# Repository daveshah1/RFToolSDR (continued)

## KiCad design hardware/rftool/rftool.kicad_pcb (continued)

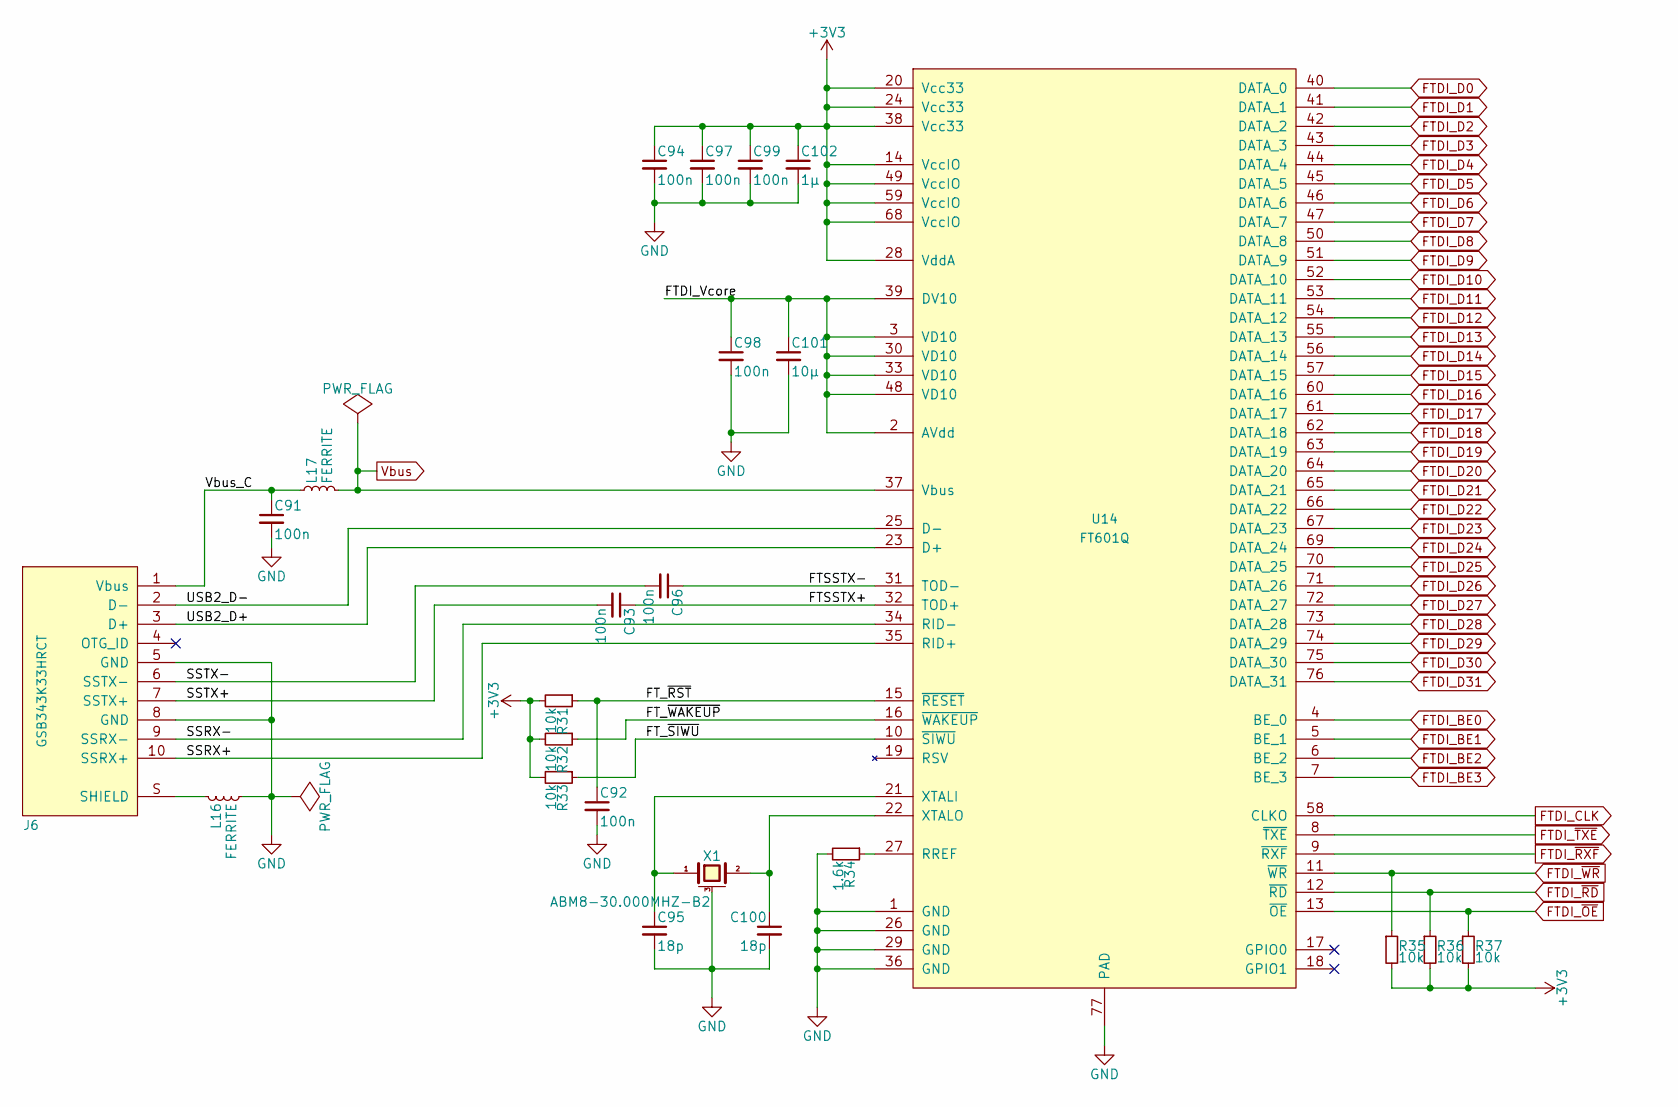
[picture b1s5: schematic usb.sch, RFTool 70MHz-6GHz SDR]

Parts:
C91, C92, C93, C94, C96, C97, C98, C99: 100n; C_0402
C95, C100: 18p; C_0402
C101: 10µ; C_0805
C102: 1µ; C_0603
J6: GSB343K33HRCT; MICROUSB-GSB343K33HRCTV
L16, L17: FERRITE; C_0805
R31, R32, R33, R35, R36, R37: 10k; R_0402
R34: 1.6k; R_0402
U14: FT601Q; QFN_76_pitch0.4mm
X1: ABM8-30.000MHZ-B2; XTAL_ABM8_3.2x2.5mm

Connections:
+3V3: C94.1, C97.1, C99.1, C102.1, R31.2, R32.2, R33.2, R35.2, R36.2, R37.2, U14.14 (VccIO), U14.20 (Vcc33), U14.24 (Vcc33), U14.28 (VddA), U14.38 (Vcc33), U14.49 (VccIO), U14.59 (VccIO), U14.68 (VccIO); also elsewhere on the board
/USB 3.0 I/F/FTDI_Vcore: C98.1, C101.1, U14.2 (AVdd), U14.3 (VD10), U14.30 (VD10), U14.33 (VD10), U14.39 (DV10), U14.48 (VD10)
/USB 3.0 I/F/FTSSTX+: C93.1, U14.32 (TOD+)
/USB 3.0 I/F/FTSSTX-: C96.1, U14.31 (TOD-)
/USB 3.0 I/F/FT_~RST: C92.1, R31.1, U14.15 (~RESET)
/USB 3.0 I/F/FT_~SIWU: R33.1, U14.10 (~SIWU)
/USB 3.0 I/F/FT_~WAKEUP: R32.1, U14.16 (~WAKEUP)
/USB 3.0 I/F/SSRX+: J6.10 (SSRX+), U14.35 (RID+)
/USB 3.0 I/F/SSRX-: J6.9 (SSRX-), U14.34 (RID-)
/USB 3.0 I/F/SSTX+: C93.2, J6.7 (SSTX+)
/USB 3.0 I/F/SSTX-: C96.2, J6.6 (SSTX-)
/USB 3.0 I/F/USB2_D+: J6.3 (D+), U14.23 (D+)
/USB 3.0 I/F/USB2_D-: J6.2 (D-), U14.25 (D-)
/USB 3.0 I/F/Vbus_C: C91.1, J6.1 (Vbus), L17.1
FTDI_BE0: U14.4 (BE_0); also elsewhere on the board
FTDI_BE1: U14.5 (BE_1); also elsewhere on the board
FTDI_BE2: U14.6 (BE_2); also elsewhere on the board
FTDI_BE3: U14.7 (BE_3); also elsewhere on the board
FTDI_CLK: U14.58 (CLKO); also elsewhere on the board
FTDI_D0: U14.40 (DATA_0); also elsewhere on the board
FTDI_D1: U14.41 (DATA_1); also elsewhere on the board
FTDI_D2: U14.42 (DATA_2); also elsewhere on the board
FTDI_D3: U14.43 (DATA_3); also elsewhere on the board
FTDI_D4: U14.44 (DATA_4); also elsewhere on the board
FTDI_D5: U14.45 (DATA_5); also elsewhere on the board
FTDI_D6: U14.46 (DATA_6); also elsewhere on the board
FTDI_D7: U14.47 (DATA_7); also elsewhere on the board
FTDI_D8: U14.50 (DATA_8); also elsewhere on the board
FTDI_D9: U14.51 (DATA_9); also elsewhere on the board
FTDI_D10: U14.52 (DATA_10); also elsewhere on the board
FTDI_D11: U14.53 (DATA_11); also elsewhere on the board
FTDI_D12: U14.54 (DATA_12); also elsewhere on the board
FTDI_D13: U14.55 (DATA_13); also elsewhere on the board
FTDI_D14: U14.56 (DATA_14); also elsewhere on the board
FTDI_D15: U14.57 (DATA_15); also elsewhere on the board
FTDI_D16: U14.60 (DATA_16); also elsewhere on the board
FTDI_D17: U14.61 (DATA_17); also elsewhere on the board
FTDI_D18: U14.62 (DATA_18); also elsewhere on the board
FTDI_D19: U14.63 (DATA_19); also elsewhere on the board
FTDI_D20: U14.64 (DATA_20); also elsewhere on the board
FTDI_D21: U14.65 (DATA_21); also elsewhere on the board
FTDI_D22: U14.66 (DATA_22); also elsewhere on the board
FTDI_D23: U14.67 (DATA_23); also elsewhere on the board
FTDI_D24: U14.69 (DATA_24); also elsewhere on the board
FTDI_D25: U14.70 (DATA_25); also elsewhere on the board
FTDI_D26: U14.71 (DATA_26); also elsewhere on the board
FTDI_D27: U14.72 (DATA_27); also elsewhere on the board
FTDI_D28: U14.73 (DATA_28); also elsewhere on the board
FTDI_D29: U14.74 (DATA_29); also elsewhere on the board
FTDI_D30: U14.75 (DATA_30); also elsewhere on the board
FTDI_D31: U14.76 (DATA_31); also elsewhere on the board
FTDI_~OE: R37.1, U14.13 (~OE); also elsewhere on the board
FTDI_~RD: R36.1, U14.12 (~RD); also elsewhere on the board
FTDI_~RXF: U14.9 (~RXF); also elsewhere on the board
FTDI_~TXE: U14.8 (~TXE); also elsewhere on the board
FTDI_~WR: R35.1, U14.11 (~WR); also elsewhere on the board
GND: C91.2, C92.2, C94.2, C95.2, C97.2, C98.2, C99.2, C100.2, C101.2, C102.2, J6.5 (GND), J6.8 (GND), L16.2, R34.2, U14.1 (GND), U14.26 (GND), U14.29 (GND), U14.36 (GND), U14.77 (PAD), X1.3 (case); also elsewhere on the board
unnamed: C95.1, U14.21 (XTALI), X1.1
unnamed: C100.1, U14.22 (XTALO), X1.2
unnamed: J6.S (SHIELD), L16.1
unnamed: R34.1, U14.27 (RREF)
Vbus: L17.2, U14.37 (Vbus); also elsewhere on the board

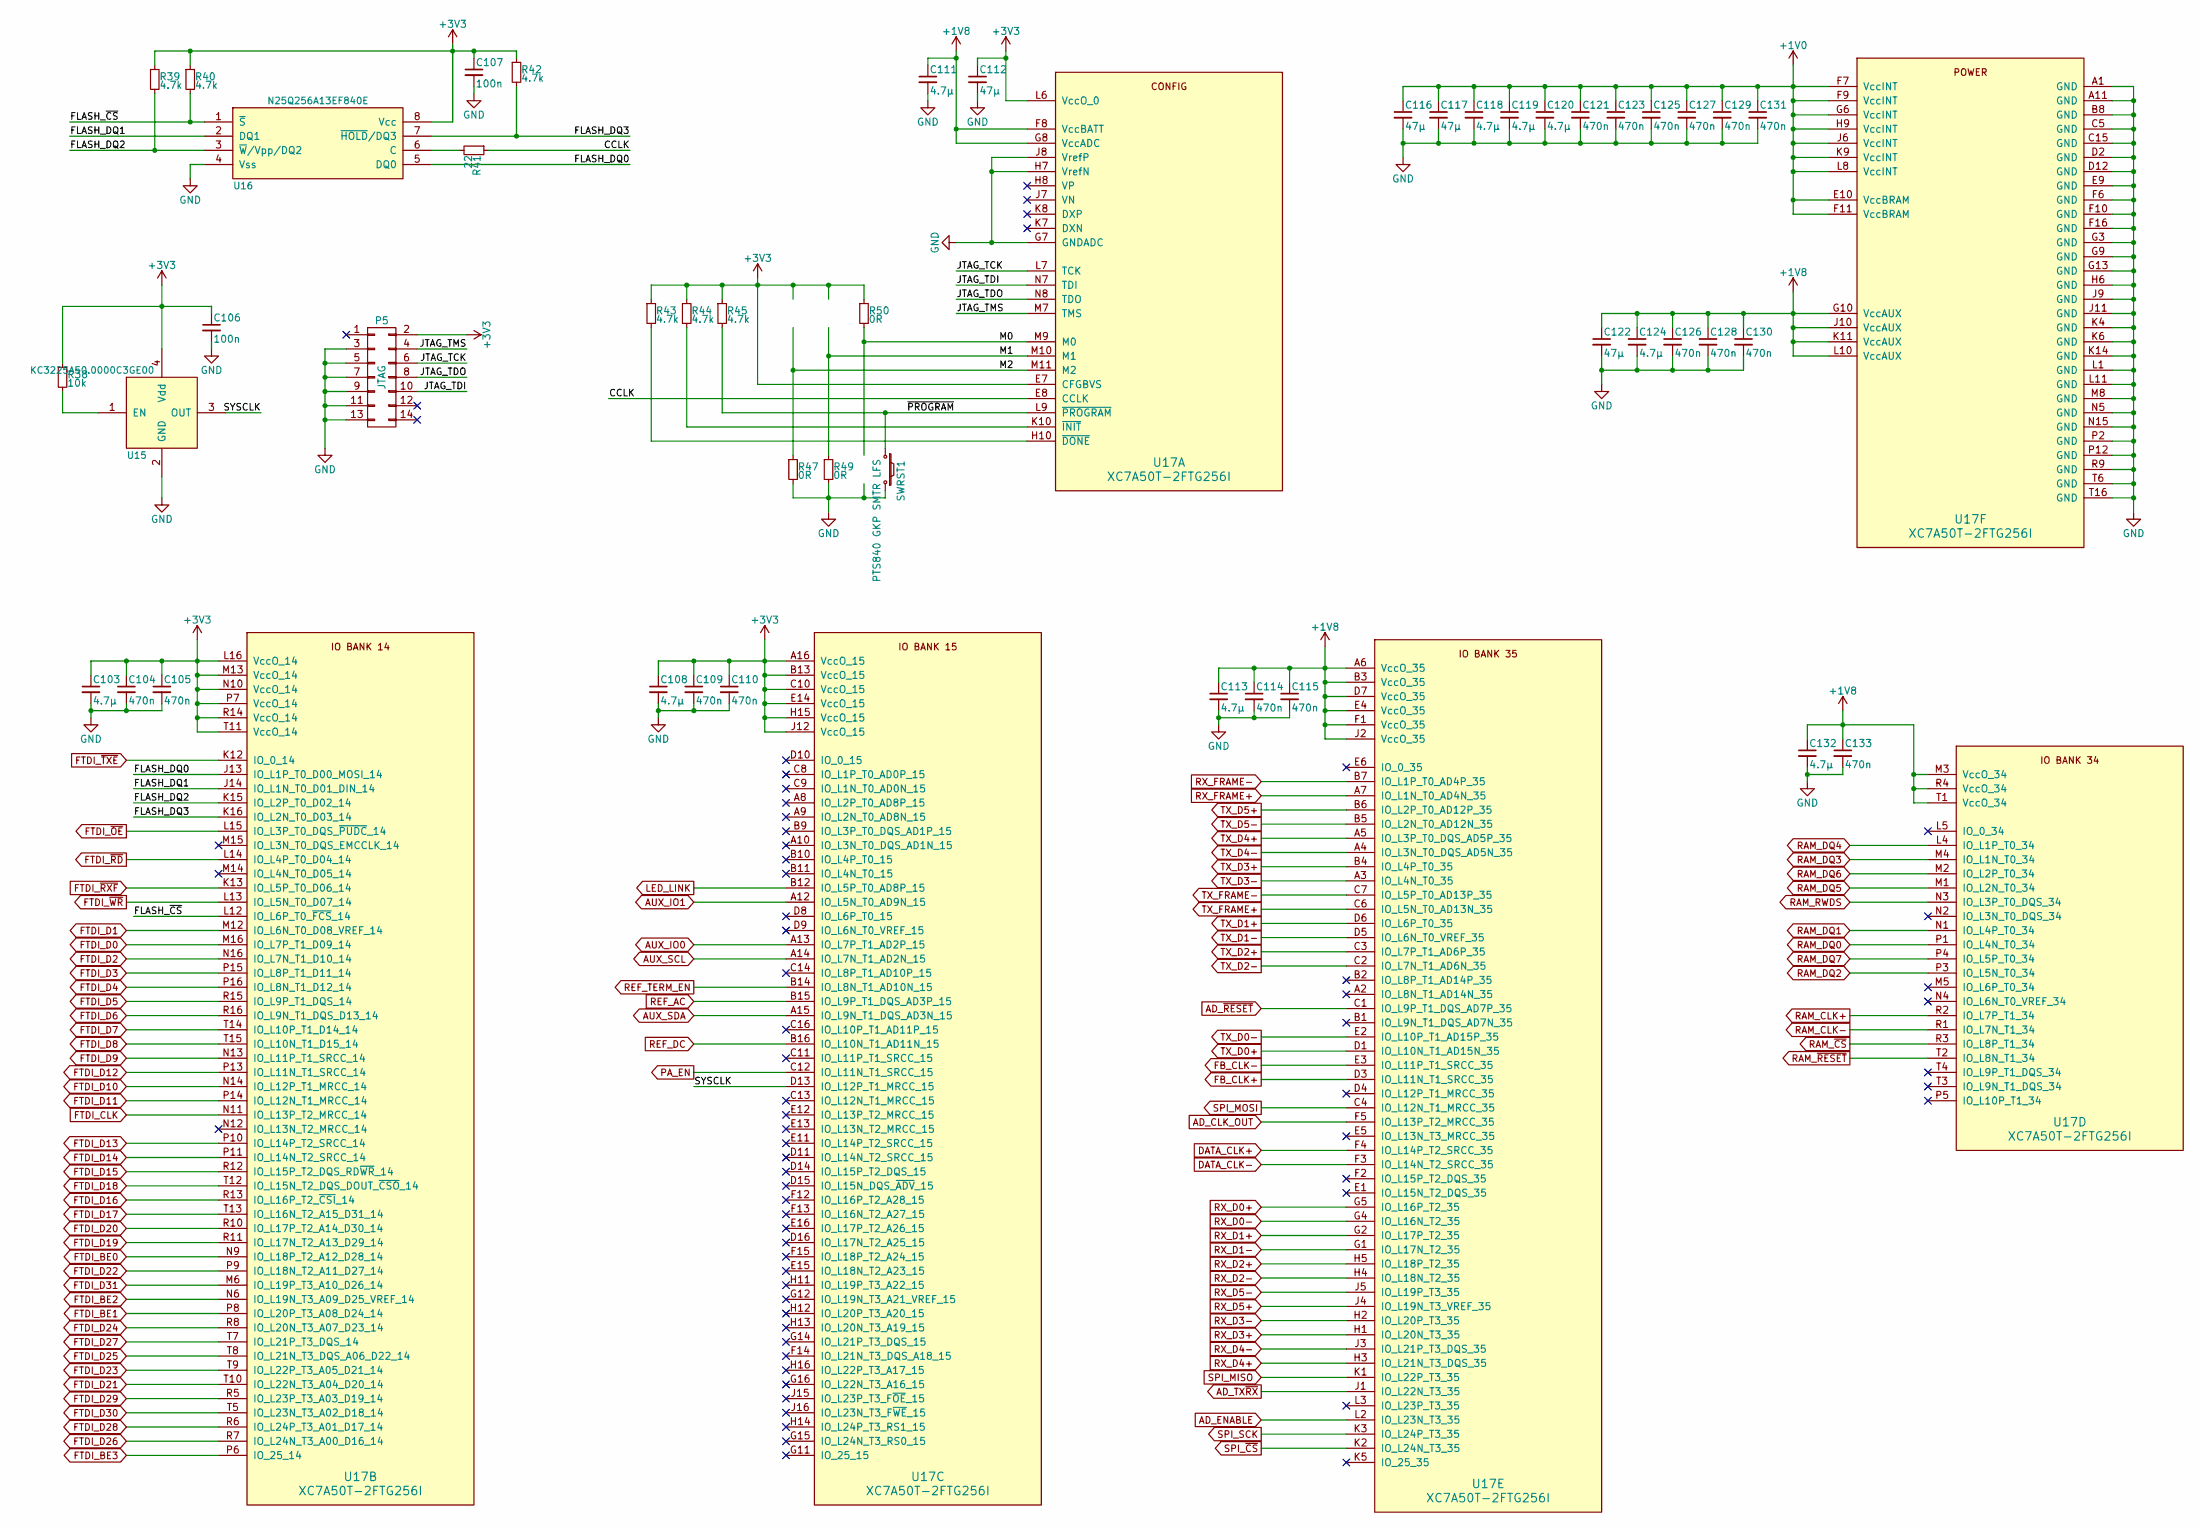
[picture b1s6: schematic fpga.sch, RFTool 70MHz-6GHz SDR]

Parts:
C103, C108, C111, C113, C118, C119, C120, C124, C132: 4.7µ; C_0805
C104, C105, C109, C110, C114, C115, C121, C123, C125, C126, C127, C128, C129, C130, C131, C133: 470n; C_0402
C106, C107: 100n; C_0402
C112, C116, C117, C122: 47µ; C_1206
P5: JTAG; Pin_Header_Straight_2x07_Pitch2.00mm
R38: 10k; R_0402
R39, R40, R42, R43, R44, R45: 4.7k; R_0402
R41: 22; R_0402
R47, R49, R50: 0R; R_0402
SWRST1: PTS840 GKP SMTR LFS; PTS840G
U15: KC3225A50.0000C3GE00; VCTCXO_TX_3.2x2.5mm
U16: N25Q256A13EF840E; VDFPN8
U17: XC7A50T-2FTG256I; BGA-256

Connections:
+1V0: C116.1, C117.1, C118.1, C119.1, C120.1, C121.1, C123.1, C125.1, C127.1, C129.1, C131.1, U17.E10 (VccBRAM), U17.F7 (VccINT), U17.F9 (VccINT), U17.F11 (VccBRAM), U17.G6 (VccINT), U17.H9 (VccINT), U17.J6 (VccINT), U17.K9 (VccINT), U17.L8 (VccINT); also elsewhere on the board
+1V8: C111.1, C113.1, C114.1, C115.1, C122.1, C124.1, C126.1, C128.1, C130.1, C132.1, C133.1, U17.A6 (VccO_35), U17.B3 (VccO_35), U17.D7 (VccO_35), U17.E4 (VccO_35), U17.F1 (VccO_35), U17.F8 (VccBATT), U17.G8 (VccADC), U17.G10 (VccAUX), U17.J2 (VccO_35), U17.J10 (VccAUX), U17.K11 (VccAUX), U17.L10 (VccAUX), U17.M3 (VccO_34), U17.R4 (VccO_34), U17.T1 (VccO_34); also elsewhere on the board
+3V3: C103.1, C104.1, C105.1, C106.1, C107.1, C108.1, C109.1, C110.1, C112.1, P5.2, R38.1, R39.1, R40.1, R42.1, R43.1, R44.1, R45.1, R50.1, U15.4 (Vdd), U16.8 (Vcc), U17.A16 (VccO_15), U17.B13 (VccO_15), U17.C10 (VccO_15), U17.E7 (CFGBVS), U17.E14 (VccO_15), U17.H15 (VccO_15), U17.J12 (VccO_15), U17.L6 (VccO_0), U17.L16 (VccO_14), U17.M13 (VccO_14), U17.N10 (VccO_14), U17.P7 (VccO_14), U17.R14 (VccO_14), U17.T11 (VccO_14); also elsewhere on the board
/Artix 7 FPGA/CCLK: R41.1, U17.E8 (CCLK)
/Artix 7 FPGA/FLASH_DQ0: U16.5 (DQ0), U17.J13 (IO_L1P_T0_D00_MOSI_14)
/Artix 7 FPGA/FLASH_DQ1: U16.2 (DQ1), U17.J14 (IO_L1N_T0_D01_DIN_14)
/Artix 7 FPGA/FLASH_DQ2: R39.2, U16.3 (~W~/Vpp/DQ2), U17.K15 (IO_L2P_T0_D02_14)
/Artix 7 FPGA/FLASH_DQ3: R42.2, U16.7 (~HOLD~/DQ3), U17.K16 (IO_L2N_T0_D03_14)
/Artix 7 FPGA/FLASH_~CS: R40.2, U16.1 (~S), U17.L12 (IO_L6P_T0_~FCS~_14)
/Artix 7 FPGA/JTAG_TCK: P5.6, U17.L7 (TCK)
/Artix 7 FPGA/JTAG_TDI: P5.10, U17.N7 (TDI)
/Artix 7 FPGA/JTAG_TDO: P5.8, U17.N8 (TDO)
/Artix 7 FPGA/JTAG_TMS: P5.4, U17.M7 (TMS)
/Artix 7 FPGA/M0: R50.2, U17.M9 (M0)
/Artix 7 FPGA/M1: R49.1, U17.M10 (M1)
/Artix 7 FPGA/M2: R47.1, U17.M11 (M2)
/Artix 7 FPGA/SYSCLK: U15.3 (OUT), U17.D13 (IO_L12P_T1_MRCC_15)
/Artix 7 FPGA/~PROGRAM: R45.2, SWRST1.1, U17.L9 (~PROGRAM)
AD_CLK_OUT: U17.F5 (IO_L13P_T2_MRCC_35); also elsewhere on the board
AD_ENABLE: U17.L2 (IO_L23N_T3_35); also elsewhere on the board
AD_TX~RX: U17.J1 (IO_L22N_T3_35); also elsewhere on the board
AD_~RESET: U17.C1 (IO_L9P_T1_DQS_AD7P_35); also elsewhere on the board
AUX_IO0: U17.A13 (IO_L7P_T1_AD2P_15); also elsewhere on the board
AUX_IO1: U17.A12 (IO_L5N_T0_AD9N_15); also elsewhere on the board
AUX_SCL: U17.A14 (IO_L7N_T1_AD2N_15); also elsewhere on the board
AUX_SDA: U17.A15 (IO_L9N_T1_DQS_AD3N_15); also elsewhere on the board
DATA_CLK+: U17.F4 (IO_L14P_T2_SRCC_35); also elsewhere on the board
DATA_CLK-: U17.F3 (IO_L14N_T2_SRCC_35); also elsewhere on the board
FB_CLK+: U17.D3 (IO_L11N_T1_SRCC_35); also elsewhere on the board
FB_CLK-: U17.E3 (IO_L11P_T1_SRCC_35); also elsewhere on the board
FTDI_BE0: U17.N9 (IO_L18P_T2_A12_D28_14); also elsewhere on the board
FTDI_BE1: U17.P8 (IO_L20P_T3_A08_D24_14); also elsewhere on the board
FTDI_BE2: U17.N6 (IO_L19N_T3_A09_D25_VREF_14); also elsewhere on the board
FTDI_BE3: U17.P6 (IO_25_14); also elsewhere on the board
FTDI_CLK: U17.N11 (IO_L13P_T2_MRCC_14); also elsewhere on the board
FTDI_D0: U17.M16 (IO_L7P_T1_D09_14); also elsewhere on the board
FTDI_D1: U17.M12 (IO_L6N_T0_D08_VREF_14); also elsewhere on the board
FTDI_D2: U17.N16 (IO_L7N_T1_D10_14); also elsewhere on the board
FTDI_D3: U17.P15 (IO_L8P_T1_D11_14); also elsewhere on the board
FTDI_D4: U17.P16 (IO_L8N_T1_D12_14); also elsewhere on the board
FTDI_D5: U17.R15 (IO_L9P_T1_DQS_14); also elsewhere on the board
FTDI_D6: U17.R16 (IO_L9N_T1_DQS_D13_14); also elsewhere on the board
FTDI_D7: U17.T14 (IO_L10P_T1_D14_14); also elsewhere on the board
FTDI_D8: U17.T15 (IO_L10N_T1_D15_14); also elsewhere on the board
FTDI_D9: U17.N13 (IO_L11P_T1_SRCC_14); also elsewhere on the board
FTDI_D10: U17.N14 (IO_L12P_T1_MRCC_14); also elsewhere on the board
FTDI_D11: U17.P14 (IO_L12N_T1_MRCC_14); also elsewhere on the board
FTDI_D12: U17.P13 (IO_L11N_T1_SRCC_14); also elsewhere on the board
FTDI_D13: U17.P10 (IO_L14P_T2_SRCC_14); also elsewhere on the board
FTDI_D14: U17.P11 (IO_L14N_T2_SRCC_14); also elsewhere on the board
FTDI_D15: U17.R12 (IO_L15P_T2_DQS_RD~WR~_14); also elsewhere on the board
FTDI_D16: U17.R13 (IO_L16P_T2_~CSI~_14); also elsewhere on the board
FTDI_D17: U17.T13 (IO_L16N_T2_A15_D31_14); also elsewhere on the board
FTDI_D18: U17.T12 (IO_L15N_T2_DQS_DOUT_~CSO~_14); also elsewhere on the board
FTDI_D19: U17.R11 (IO_L17N_T2_A13_D29_14); also elsewhere on the board
FTDI_D20: U17.R10 (IO_L17P_T2_A14_D30_14); also elsewhere on the board
FTDI_D21: U17.T10 (IO_L22N_T3_A04_D20_14); also elsewhere on the board
FTDI_D22: U17.P9 (IO_L18N_T2_A11_D27_14); also elsewhere on the board
FTDI_D23: U17.T9 (IO_L22P_T3_A05_D21_14); also elsewhere on the board
FTDI_D24: U17.R8 (IO_L20N_T3_A07_D23_14); also elsewhere on the board
FTDI_D25: U17.T8 (IO_L21N_T3_DQS_A06_D22_14); also elsewhere on the board
FTDI_D26: U17.R7 (IO_L24N_T3_A00_D16_14); also elsewhere on the board
FTDI_D27: U17.T7 (IO_L21P_T3_DQS_14); also elsewhere on the board
FTDI_D28: U17.R6 (IO_L24P_T3_A01_D17_14); also elsewhere on the board
FTDI_D29: U17.R5 (IO_L23P_T3_A03_D19_14); also elsewhere on the board
FTDI_D30: U17.T5 (IO_L23N_T3_A02_D18_14); also elsewhere on the board
FTDI_D31: U17.M6 (IO_L19P_T3_A10_D26_14); also elsewhere on the board
FTDI_~OE: U17.L15 (IO_L3P_T0_DQS_~PUDC~_14); also elsewhere on the board
FTDI_~RD: U17.L14 (IO_L4P_T0_D04_14); also elsewhere on the board
FTDI_~RXF: U17.K13 (IO_L5P_T0_D06_14); also elsewhere on the board
FTDI_~TXE: U17.K12 (IO_0_14); also elsewhere on the board
FTDI_~WR: U17.L13 (IO_L5N_T0_D07_14); also elsewhere on the board
GND: C103.2, C104.2, C105.2, C106.2, C107.2, C108.2, C109.2, C110.2, C111.2, C112.2, C113.2, C114.2, C115.2, C116.2, C117.2, C118.2, C119.2, C120.2, C121.2, C122.2, C123.2, C124.2, C125.2, C126.2, C127.2, C128.2, C129.2, C130.2, C131.2, C132.2, C133.2, P5.3, P5.5, P5.7, P5.9, P5.11, P5.13, R47.2, R49.2, SWRST1.2, U15.2 (GND), U16.4 (Vss), U17.A1 (GND), U17.A11 (GND), U17.B8 (GND), U17.C5 (GND), U17.C15 (GND), U17.D2 (GND), U17.D12 (GND), U17.E9 (GND), U17.F6 (GND), U17.F10 (GND), U17.F16 (GND), U17.G3 (GND), U17.G7 (GNDADC), U17.G9 (GND), U17.G13 (GND), U17.H6 (GND), U17.H7 (VrefN), U17.J8 (VrefP), U17.J9 (GND), U17.J11 (GND), U17.K4 (GND), U17.K6 (GND), U17.K14 (GND), U17.L1 (GND), U17.L11 (GND), U17.M8 (GND), U17.N5 (GND), U17.N15 (GND), U17.P2 (GND), U17.P12 (GND), U17.R9 (GND), U17.T6 (GND), U17.T16 (GND); also elsewhere on the board
LED_LINK: U17.B12 (IO_L5P_T0_AD8P_15); also elsewhere on the board
unnamed: R38.2, U15.1 (EN)
unnamed: R41.2, U16.6 (C)
unnamed: R43.2, U17.H10 (~DONE)
unnamed: R44.2, U17.K10 (~INIT)
PA_EN: U17.C12 (IO_L11N_T1_SRCC_15); also elsewhere on the board
RAM_CLK+: U17.R2 (IO_L7P_T1_34); also elsewhere on the board
RAM_CLK-: U17.R1 (IO_L7N_T1_34); also elsewhere on the board
RAM_DQ0: U17.P1 (IO_L4N_T0_34); also elsewhere on the board
RAM_DQ1: U17.N1 (IO_L4P_T0_34); also elsewhere on the board
RAM_DQ2: U17.P3 (IO_L5N_T0_34); also elsewhere on the board
RAM_DQ3: U17.M4 (IO_L1N_T0_34); also elsewhere on the board
RAM_DQ4: U17.L4 (IO_L1P_T0_34); also elsewhere on the board
RAM_DQ5: U17.M1 (IO_L2N_T0_34); also elsewhere on the board
RAM_DQ6: U17.M2 (IO_L2P_T0_34); also elsewhere on the board
RAM_DQ7: U17.P4 (IO_L5P_T0_34); also elsewhere on the board
RAM_RWDS: U17.N3 (IO_L3P_T0_DQS_34); also elsewhere on the board
RAM_~CS: U17.R3 (IO_L8P_T1_34); also elsewhere on the board
RAM_~RESET: U17.T2 (IO_L8N_T1_34); also elsewhere on the board
REF_AC: U17.B15 (IO_L9P_T1_DQS_AD3P_15); also elsewhere on the board
REF_DC: U17.B16 (IO_L10N_T1_AD11N_15); also elsewhere on the board
REF_TERM_EN: U17.B14 (IO_L8N_T1_AD10N_15); also elsewhere on the board
RX_D0+: U17.G5 (IO_L16P_T2_35); also elsewhere on the board
RX_D0-: U17.G4 (IO_L16N_T2_35); also elsewhere on the board
RX_D1+: U17.G2 (IO_L17P_T2_35); also elsewhere on the board
RX_D1-: U17.G1 (IO_L17N_T2_35); also elsewhere on the board
RX_D2+: U17.H5 (IO_L18P_T2_35); also elsewhere on the board
RX_D2-: U17.H4 (IO_L18N_T2_35); also elsewhere on the board
RX_D3+: U17.H1 (IO_L20N_T3_35); also elsewhere on the board
RX_D3-: U17.H2 (IO_L20P_T3_35); also elsewhere on the board
RX_D4+: U17.H3 (IO_L21N_T3_DQS_35); also elsewhere on the board
RX_D4-: U17.J3 (IO_L21P_T3_DQS_35); also elsewhere on the board
RX_D5+: U17.J4 (IO_L19N_T3_VREF_35); also elsewhere on the board
RX_D5-: U17.J5 (IO_L19P_T3_35); also elsewhere on the board
RX_FRAME+: U17.A7 (IO_L1N_T0_AD4N_35); also elsewhere on the board
RX_FRAME-: U17.B7 (IO_L1P_T0_AD4P_35); also elsewhere on the board
SPI_MISO: U17.K1 (IO_L22P_T3_35); also elsewhere on the board
SPI_MOSI: U17.C4 (IO_L12N_T1_MRCC_35); also elsewhere on the board
SPI_SCK: U17.K3 (IO_L24P_T3_35); also elsewhere on the board
SPI_~CS: U17.K2 (IO_L24N_T3_35); also elsewhere on the board
TX_D0+: U17.D1 (IO_L10N_T1_AD15N_35); also elsewhere on the board
TX_D0-: U17.E2 (IO_L10P_T1_AD15P_35); also elsewhere on the board
TX_D1+: U17.D6 (IO_L6P_T0_35); also elsewhere on the board
TX_D1-: U17.D5 (IO_L6N_T0_VREF_35); also elsewhere on the board
TX_D2+: U17.C3 (IO_L7P_T1_AD6P_35); also elsewhere on the board
TX_D2-: U17.C2 (IO_L7N_T1_AD6N_35); also elsewhere on the board
TX_D3+: U17.B4 (IO_L4P_T0_35); also elsewhere on the board
TX_D3-: U17.A3 (IO_L4N_T0_35); also elsewhere on the board
TX_D4+: U17.A5 (IO_L3P_T0_DQS_AD5P_35); also elsewhere on the board
TX_D4-: U17.A4 (IO_L3N_T0_DQS_AD5N_35); also elsewhere on the board
TX_D5+: U17.B6 (IO_L2P_T0_AD12P_35); also elsewhere on the board
TX_D5-: U17.B5 (IO_L2N_T0_AD12N_35); also elsewhere on the board
TX_FRAME+: U17.C6 (IO_L5N_T0_AD13N_35); also elsewhere on the board
TX_FRAME-: U17.C7 (IO_L5P_T0_AD13P_35); also elsewhere on the board

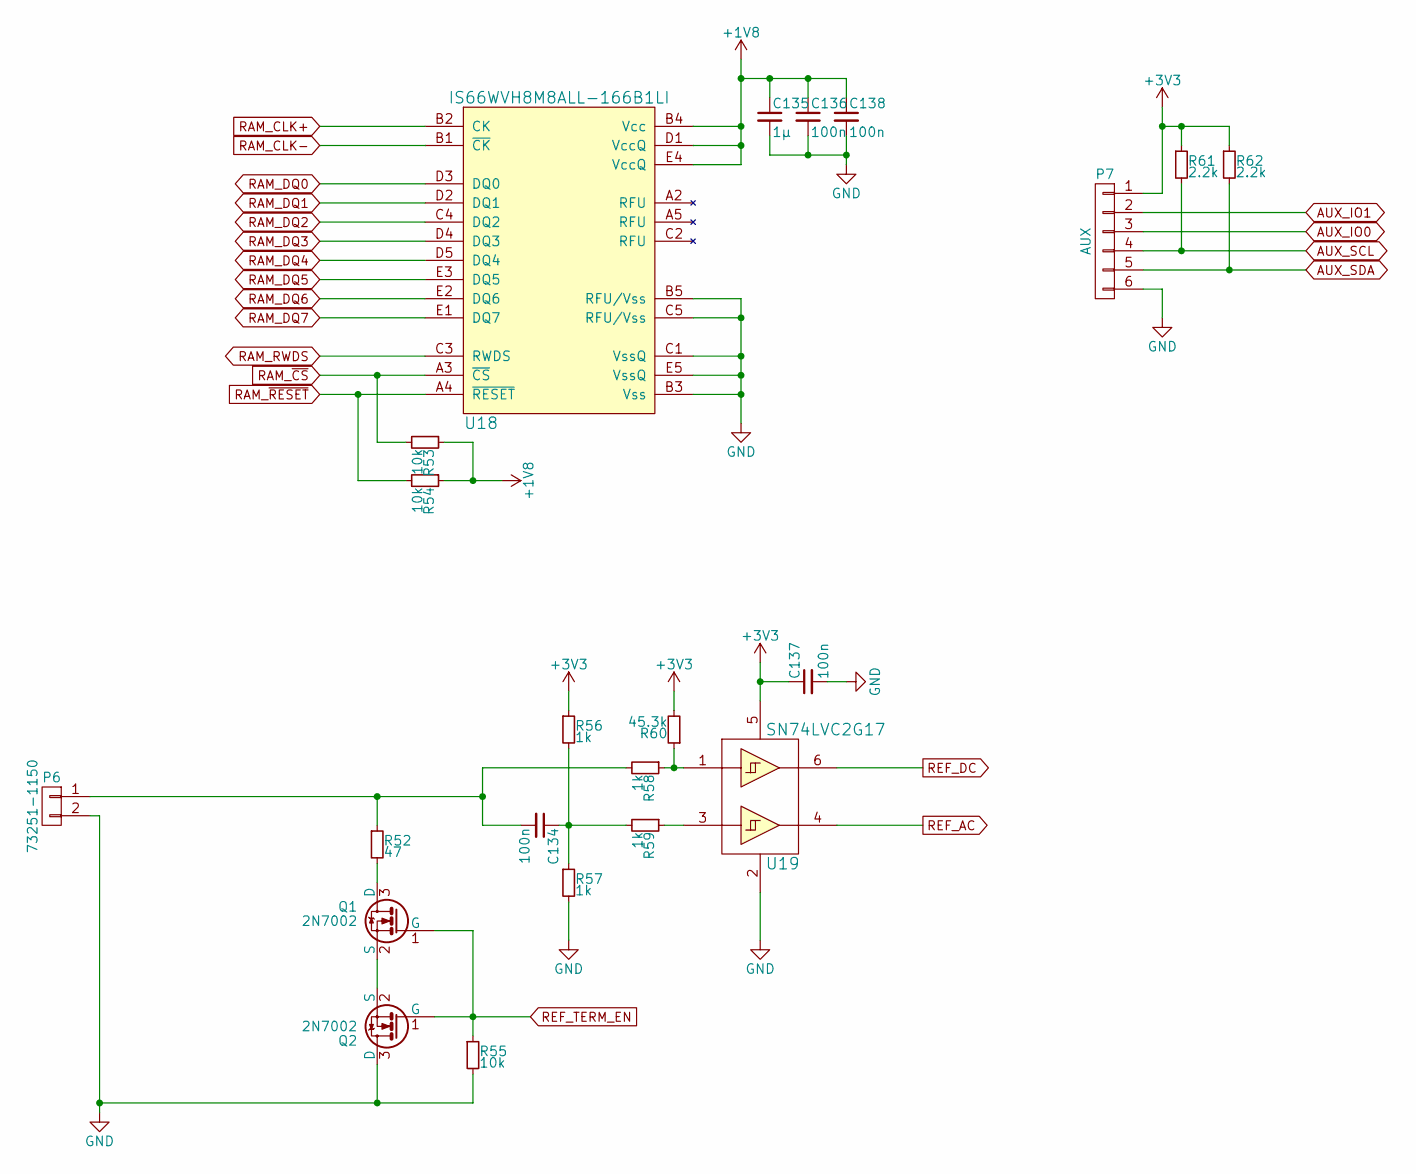
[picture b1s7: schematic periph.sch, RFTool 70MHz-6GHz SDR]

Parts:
C134, C136, C137, C138: 100n; C_0402
C135: 1µ; C_0603
P6: 73251-1150; SMA-EDGE-73251-1150
P7: AUX; Pin_Header_Angled_1x06
Q1, Q2: 2N7002; SOT-23
R52: 47; R_0402
R53, R54, R55: 10k; R_0402
R56, R57, R58, R59: 1k; R_0402
R60: 45.3k; R_0402
R61, R62: 2.2k; R_0402
U18: IS66WVH8M8ALL-166B1LI; FBGA24_pitch1mm
U19: SN74LVC2G17; SOT-23-6

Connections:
+1V8: C135.1, C136.1, C138.1, R53.1, R54.1, U18.B4 (Vcc), U18.D1 (VccQ), U18.E4 (VccQ); also elsewhere on the board
+3V3: C137.1, P7.1, R56.1, R60.2, R61.1, R62.1, U19.5 (Vcc); also elsewhere on the board
AUX_IO0: P7.3; also elsewhere on the board
AUX_IO1: P7.2; also elsewhere on the board
AUX_SCL: P7.4, R61.2; also elsewhere on the board
AUX_SDA: P7.5, R62.2; also elsewhere on the board
GND: C135.2, C136.2, C137.2, C138.2, P6.2, P7.6, Q2.3 (D), R55.2, R57.2, U18.B3 (Vss), U18.B5 (RFU/Vss), U18.C1 (VssQ), U18.C5 (RFU/Vss), U18.E5 (VssQ), U19.2 (GND); also elsewhere on the board
unnamed: C134.1, R56.2, R57.1, R59.2
unnamed: C134.2, P6.1, R52.1, R58.2
unnamed: Q1.2 (S), Q2.2 (S)
unnamed: Q1.3 (D), R52.2
unnamed: R58.1, R60.1, U19.1 (1A)
unnamed: R59.1, U19.3 (2A)
RAM_CLK+: U18.B2 (CK); also elsewhere on the board
RAM_CLK-: U18.B1 (~CK); also elsewhere on the board
RAM_DQ0: U18.D3 (DQ0); also elsewhere on the board
RAM_DQ1: U18.D2 (DQ1); also elsewhere on the board
RAM_DQ2: U18.C4 (DQ2); also elsewhere on the board
RAM_DQ3: U18.D4 (DQ3); also elsewhere on the board
RAM_DQ4: U18.D5 (DQ4); also elsewhere on the board
RAM_DQ5: U18.E3 (DQ5); also elsewhere on the board
RAM_DQ6: U18.E2 (DQ6); also elsewhere on the board
RAM_DQ7: U18.E1 (DQ7); also elsewhere on the board
RAM_RWDS: U18.C3 (RWDS); also elsewhere on the board
RAM_~CS: R53.2, U18.A3 (~CS); also elsewhere on the board
RAM_~RESET: R54.2, U18.A4 (~RESET); also elsewhere on the board
REF_AC: U19.4 (Y); also elsewhere on the board
REF_DC: U19.6 (1Y); also elsewhere on the board
REF_TERM_EN: Q1.1 (G), Q2.1 (G), R55.1; also elsewhere on the board

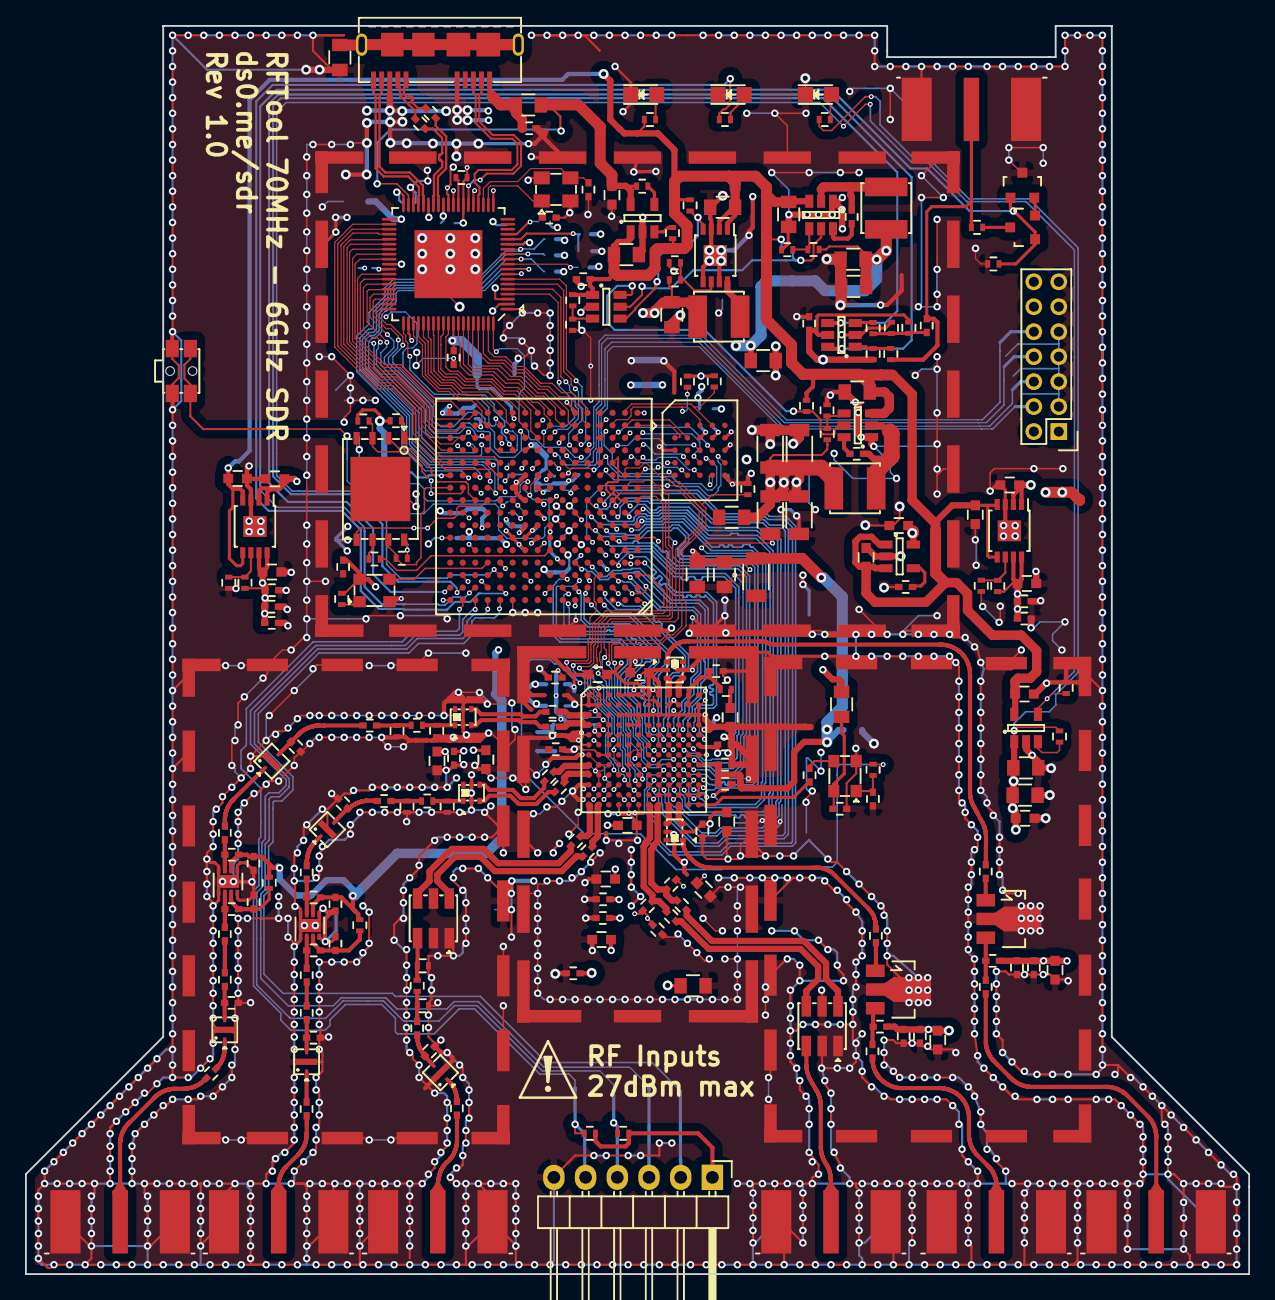
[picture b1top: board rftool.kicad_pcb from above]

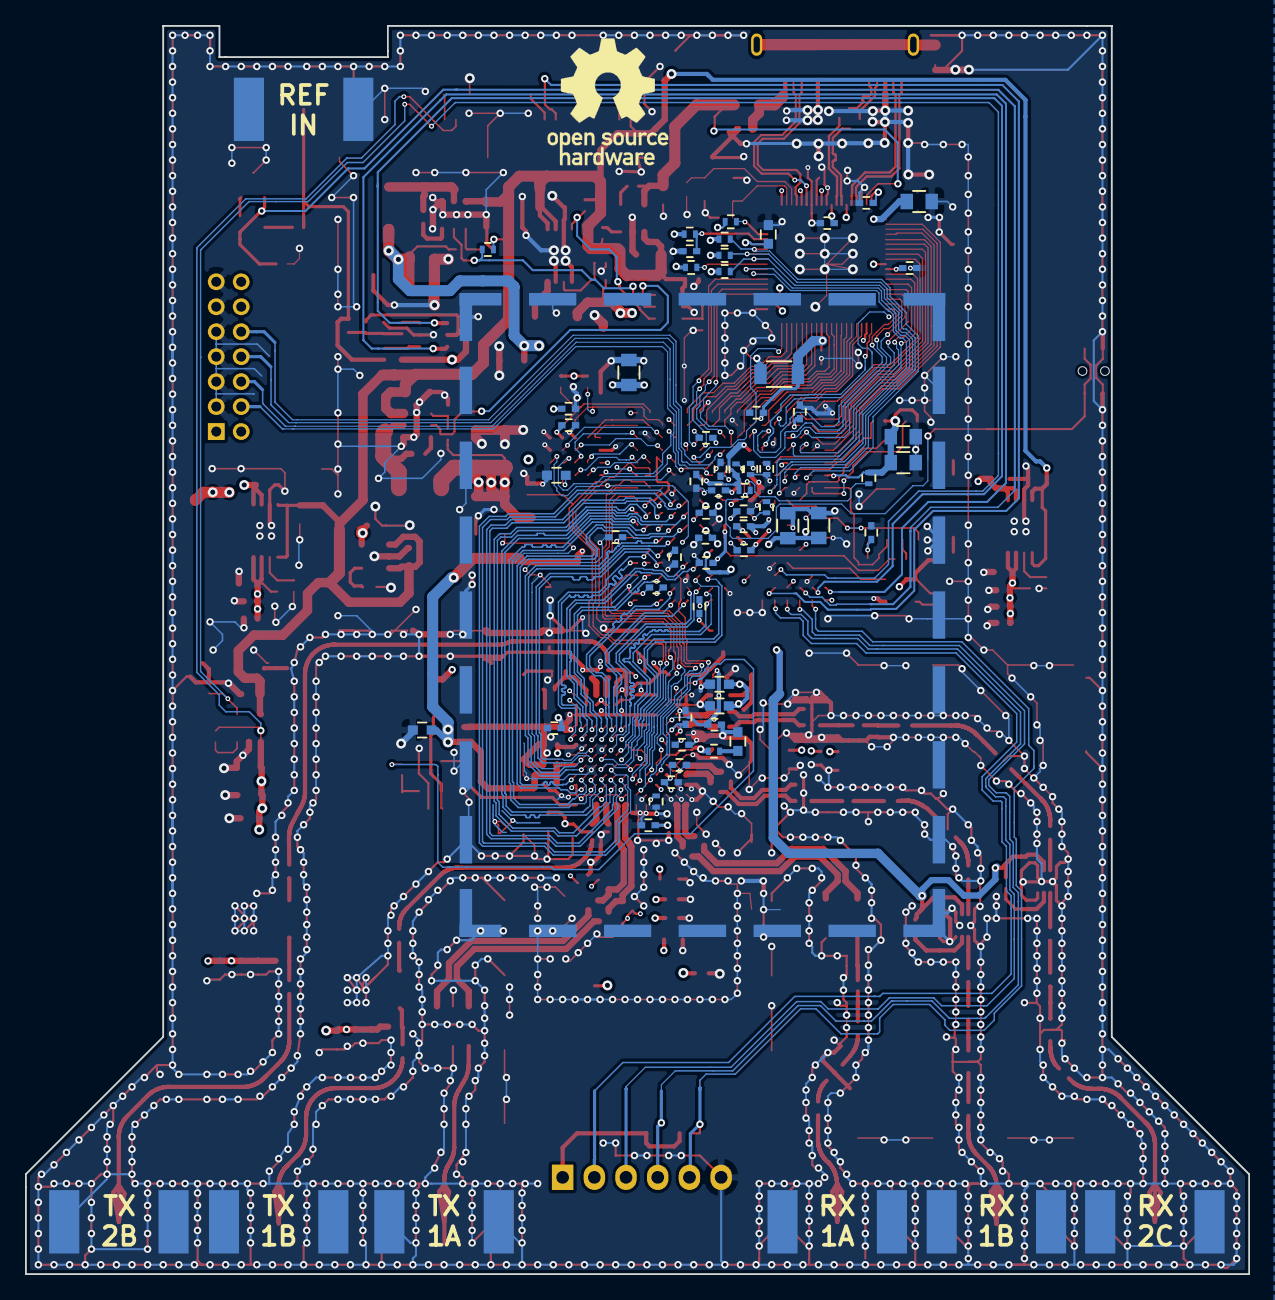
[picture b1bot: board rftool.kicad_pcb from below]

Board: 4 copper layers, 98.0 x 100.0 mm, 290 parts (59 on the bottom side), 243 nets.

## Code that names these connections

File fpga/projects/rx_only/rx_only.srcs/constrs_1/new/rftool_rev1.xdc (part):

set_property PACKAGE_PIN F5 [get_ports ad_clock]
set_property PACKAGE_PIN F3 [get_ports ad_data_clock_n]
set_property PACKAGE_PIN F4 [get_ports ad_data_clock_p]
set_property PACKAGE_PIN L2 [get_ports ad_enable]
set_property PACKAGE_PIN D3 [get_ports ad_fb_clock_p]
set_property PACKAGE_PIN E3 [get_ports ad_fb_clock_n]
set_property PACKAGE_PIN D1 [get_ports {ad_p0_d[1]}]
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set_property PACKAGE_PIN H3 [get_ports {ad_p1_d[9]}]
set_property PACKAGE_PIN J4 [get_ports {ad_p1_d[11]}]
set_property PACKAGE_PIN J5 [get_ports {ad_p1_d[10]}]
set_property PACKAGE_PIN C1 [get_ports ad_reset]
set_property PACKAGE_PIN B7 [get_ports ad_rx_frame_n]
set_property PACKAGE_PIN A7 [get_ports ad_rx_frame_p]
set_property PACKAGE_PIN K3 [get_ports ad_spi_clk]
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set_property PACKAGE_PIN C7 [get_ports ad_tx_frame_n]
set_property PACKAGE_PIN C6 [get_ports ad_tx_frame_p]
set_property PACKAGE_PIN J1 [get_ports ad_txnrx]
set_property PACKAGE_PIN A13 [get_ports aux_io0]
set_property PACKAGE_PIN A12 [get_ports aux_io1]
set_property PACKAGE_PIN A14 [get_ports aux_scl]
set_property PACKAGE_PIN A15 [get_ports aux_sda]
set_property PACKAGE_PIN N9 [get_ports {ftdi_be[0]}]
set_property PACKAGE_PIN P8 [get_ports {ftdi_be[1]}]
set_property PACKAGE_PIN N6 [get_ports {ftdi_be[2]}]
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set_property PACKAGE_PIN K13 [get_ports ftdi_rxf_n]
set_property PACKAGE_PIN K12 [get_ports ftdi_txe_n]
set_property PACKAGE_PIN L13 [get_ports ftdi_wr_n]
set_property PACKAGE_PIN B12 [get_ports led_link]
set_property PACKAGE_PIN C12 [get_ports pa_en]
set_property PACKAGE_PIN R1 [get_ports ram_clk_n]
set_property PACKAGE_PIN R2 [get_ports ram_clk_p]
set_property PACKAGE_PIN R3 [get_ports ram_csn]
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set_property PACKAGE_PIN M2 [get_ports {ram_dq[6]}]
set_property PACKAGE_PIN P4 [get_ports {ram_dq[7]}]
set_property PACKAGE_PIN T2 [get_ports ram_rstn]
set_property PACKAGE_PIN N3 [get_ports ram_rwds]
set_property PACKAGE_PIN B15 [get_ports ref_ac]
set_property PACKAGE_PIN B16 [get_ports ref_dc]
set_property PACKAGE_PIN B14 [get_ports ref_term_en]
set_property PACKAGE_PIN D13 [get_ports sys_clock_in]
set_property IOSTANDARD LVCMOS33 [get_ports ftdi_wr_n]
set_property IOSTANDARD LVCMOS33 [get_ports {ftdi_data[18]}]
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
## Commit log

2016-12-20 Hardware Rev 1.0
2016-12-24 Update Errata after more testing
2017-01-16 Add rx-only FPGA project and Linux demo app
2017-01-16 Improve responsivity at lower sample rates
2017-01-22 Add a basic waterfall style display to the UI
2017-04-15 FPGA tweaks to improve performance, and preparation for TX support
2017-04-15 Linux App Improvements
    - Fix some memory access bugs
    - Add optional support for CUDA FFTs
    - Compile a shared library, as part of a gnuradio integration project
2017-10-03 Add DDS and noise signal generator, plus WIP demodulation
